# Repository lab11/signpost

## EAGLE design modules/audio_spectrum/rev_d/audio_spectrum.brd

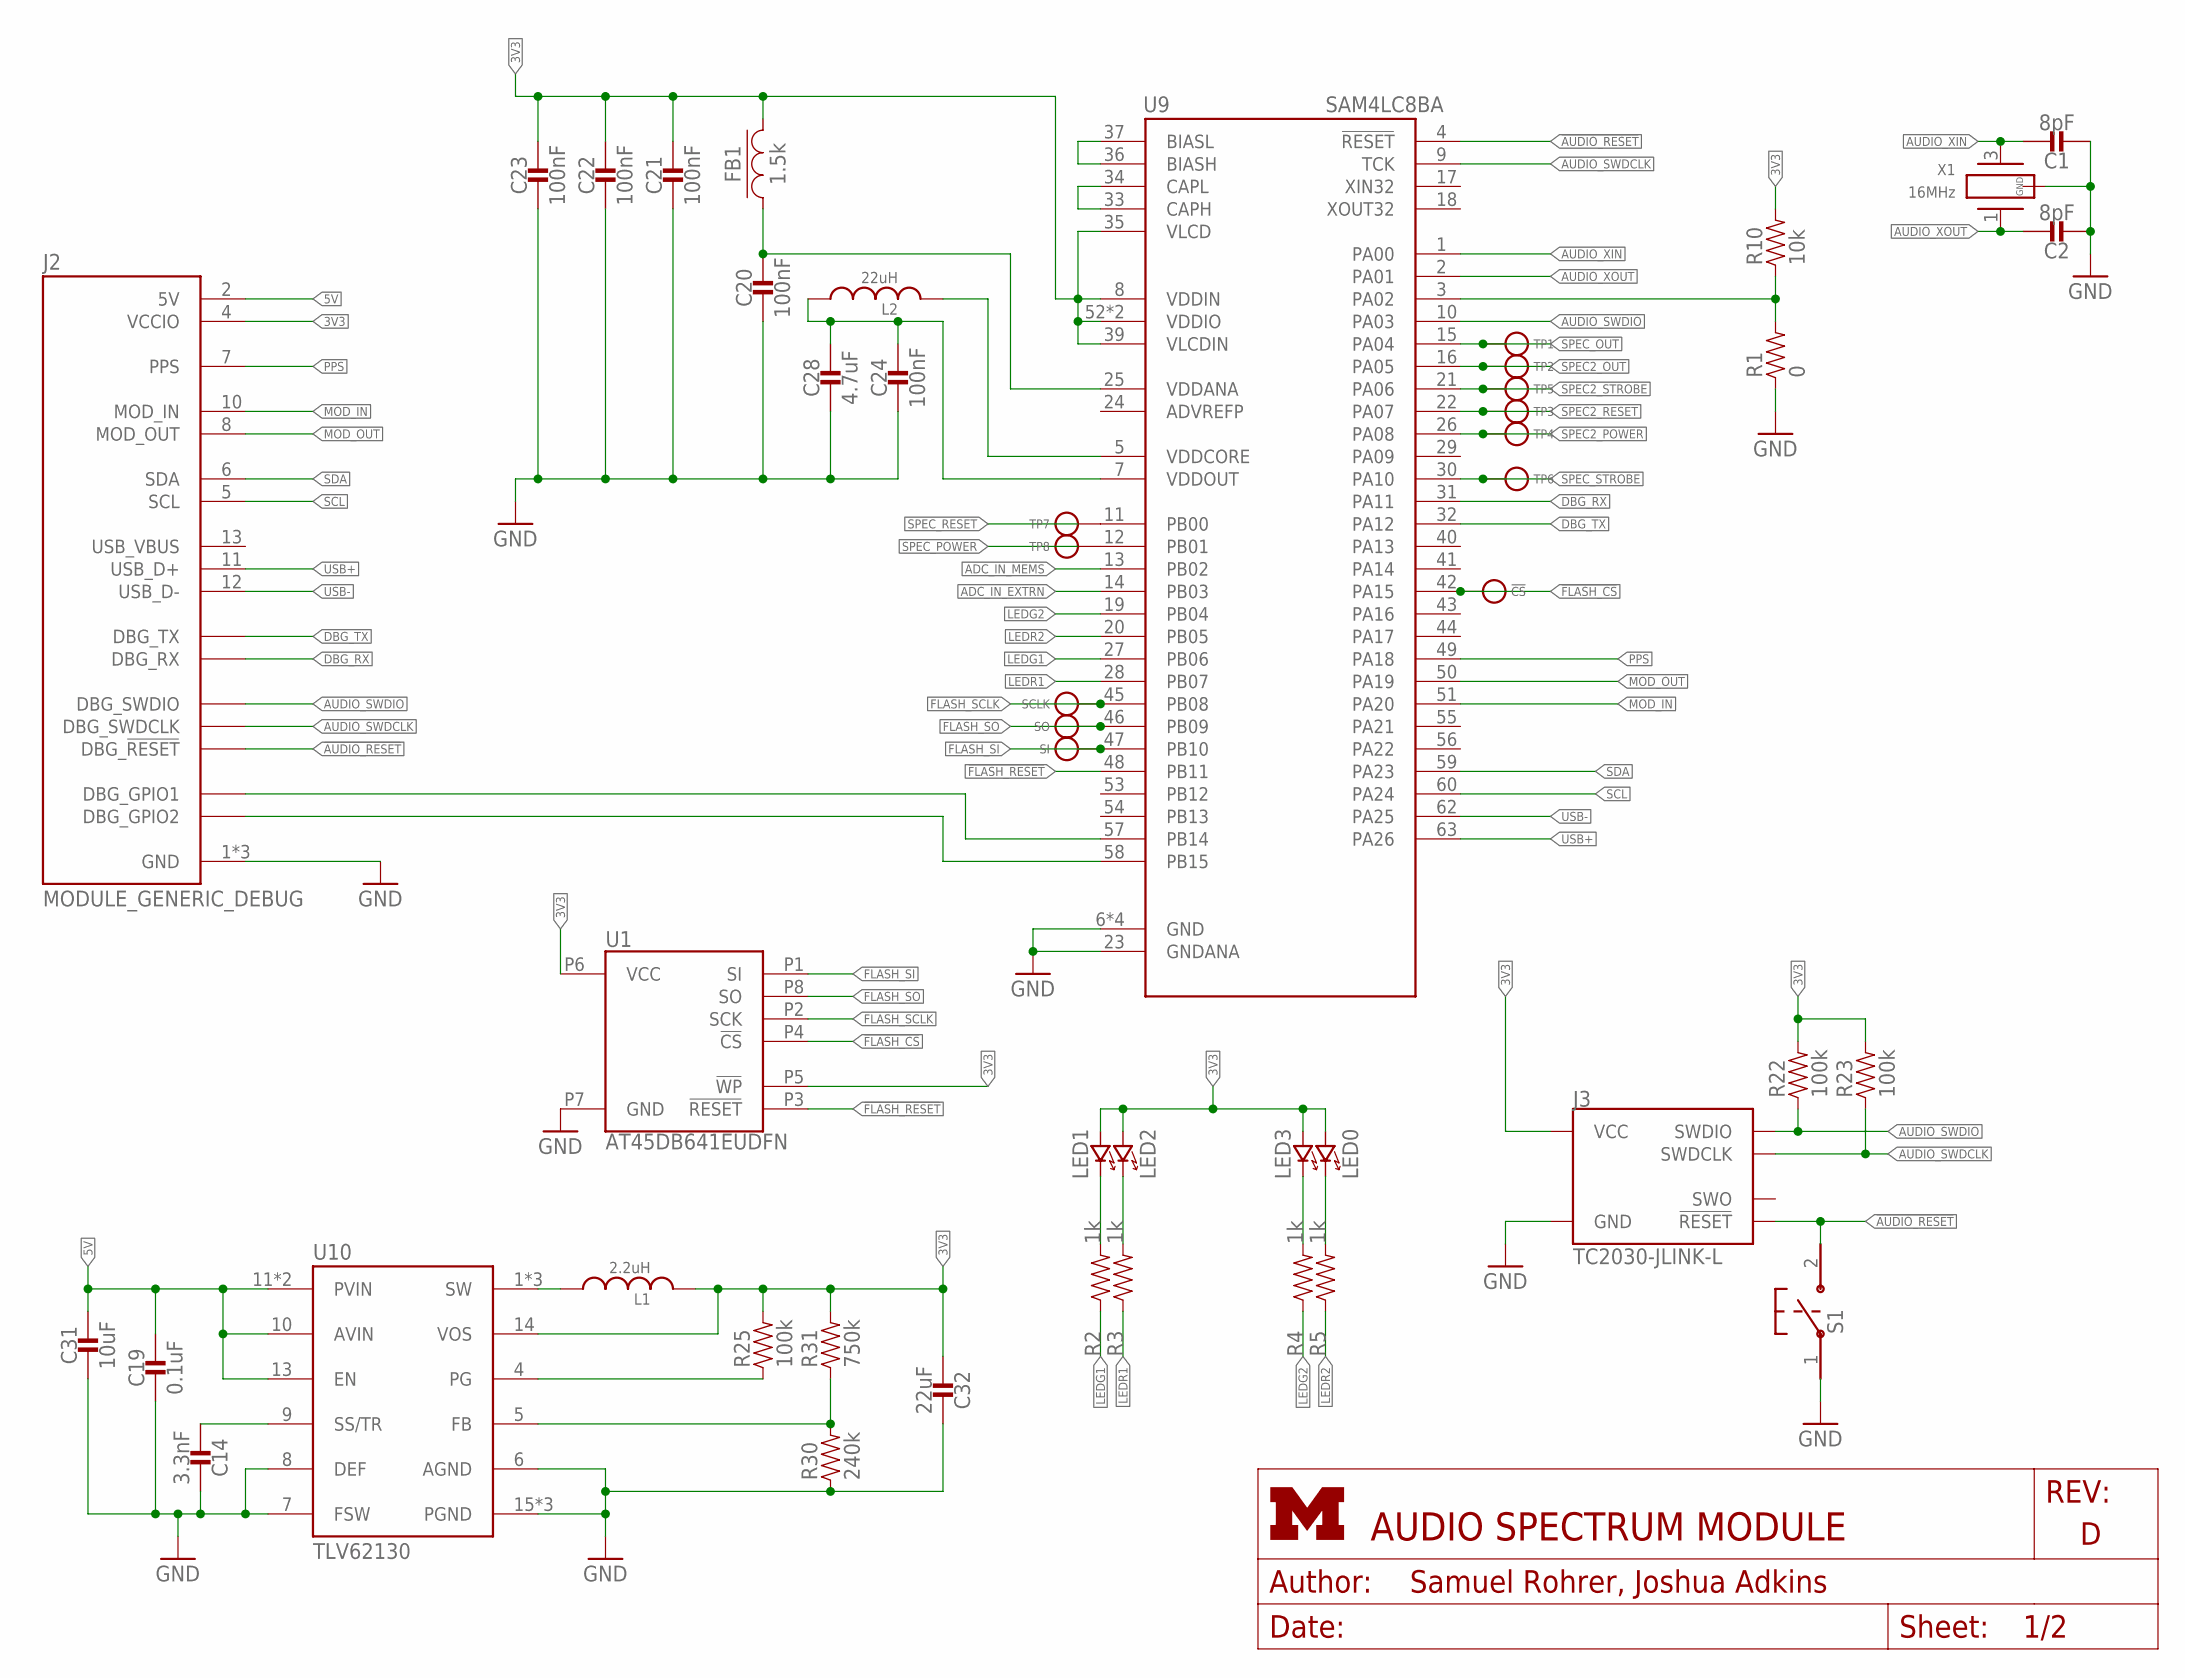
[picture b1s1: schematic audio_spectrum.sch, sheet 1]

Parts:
!CS: TEST_POINT_0.040IN; TESTPOINT_0.040IN
C1, C2: 8pF; 0402_CAP; DIGIKEY 490-8230-1-ND
C14: 3.3nF; 0603_CAP; DIGIKEY 490-1503-1-ND
C19: 0.1uF; 0603_CAP; DIGIKEY 490-1532-1-ND
C20, C21, C22, C23: 100nF; 0603_CAP; DIGIKEY 490-1532-1-ND
C24: 100nF; 0402_CAP; DIGIKEY 490-10777-1-ND
C28: 4.7uF; 0402_CAP; DIGIKEY 490-13252-1-ND
C31: 10uF; 0603_CAP; DIGIKEY 490-6405-1-ND
C32: 22uF; 0603_CAP; DIGIKEY 490-13241-1-ND
FB1: 1.5k; 0402_CAP; DIGIKEY 490-5216-1-ND
J2: MODULE_GENERIC_DEBUG
J3: TC2030-JLINK-L; TC2030-IDC
L1: 2.2uH; IHL-1212BZ-11
L2: 22uH; 1212
LED0, LED2: LED0603; LED-0603; DIGIKEY 160-1447-1-ND
LED1, LED3: LED0603; LED-0603; DIGIKEY 160-1446-1-ND
R1: 0; 0603-RES; DIGIKEY 1276-3431-1-ND
R2: 1k; 0603-RES; DIGIKEY RHM1.0KDCT-N
R3, R4, R5: 1k; 0603-RES; DIGIKEY RHM1.0KDCT-ND
R10: 10k; 0603-RES; DIGIKEY RHM10.0KHCT-ND
R22, R23, R25: 100k; 0603-RES; DIGIKEY RHM100KCGCT-ND
R30: 240k; 0603-RES; DIGIKEY RHM240KCFCT-ND
R31: 750k; 0603-RES; DIGIKEY RHM750KCFCT-ND
S1: B3U-1000P
SCLK: TEST_POINT_0.040IN; TESTPOINT_0.040IN
SI: TEST_POINT_0.040IN; TESTPOINT_0.040IN
SO: TEST_POINT_0.040IN; TESTPOINT_0.040IN
TP1, TP2, TP3, TP4, TP5, TP6, TP7, TP8: TEST_POINT_0.040IN; TESTPOINT_0.040IN
U1: AT45DB641EUDFN; UDFN-8-5MMX6MM
U9: SAM4LC8BA; QFN-64-9MM
U10: TLV62130; TQFN-16/3MM
X1: 16MHz; FHXXX

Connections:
3V3: C21.1, C22.1, C23.1, C32.2, FB1.2, J2.4 (VCCIO), J3.1 (VCC), L1.P$2 (2), LED0.A (ANODE), LED1.A (ANODE), LED2.A (ANODE), LED3.A (ANODE), R10.2, R22.2, R23.2, R25.2, R31.2, U1.P5 (!WP), U1.P6 (VCC), U9.8 (VDDIN), U9.35 (VLCD), U9.39 (VLCDIN), U9.52 (VDDIO), U9.61 (VDDIO), U10.14 (VOS); also elsewhere on the board
3VSWOUT: L1.P$1 (1), U10.1 (SW), U10.2 (SW), U10.3 (SW)
5V: C19.1, C31.1, J2.2 (5V), U10.10 (AVIN), U10.11 (PVIN), U10.12 (PVIN), U10.13 (EN)
!AUDIO_RESET: J2.20 (DBG_!RESET), J3.3 (!RESET), S1.2, U9.4 (!RESET)
!FLASH_CS: !CS.TESTPOINT, U1.P4 (!CS), U9.42 (PA15)
!FLASH_RESET: U1.P3 (!RESET), U9.48 (PB11)
ADC_IN_EXTRN: U9.14 (PB03); also elsewhere on the board
ADC_IN_MEMS: U9.13 (PB02); also elsewhere on the board
AUDIO_SWDCLK: J2.21 (DBG_SWDCLK), J3.4 (SWDCLK), R23.1, U9.9 (TCK)
AUDIO_SWDIO: J2.22 (DBG_SWDIO), J3.2 (SWDIO), R22.1, U9.10 (PA03)
AUDIO_XIN: C1.1, U9.1 (PA00), X1.3 (2)
AUDIO_XOUT: C2.1, U9.2 (PA01), X1.1
CONTROLLER_BUCK/LDO_N: R1.2, R10.1, U9.3 (PA02)
DBG_GPIO1: J2.16 (DBG_GPIO1), U9.57 (PB14)
DBG_GPIO2: J2.19 (DBG_GPIO2), U9.58 (PB15)
DBG_RX: J2.18 (DBG_RX), U9.31 (PA11)
DBG_TX: J2.17 (DBG_TX), U9.32 (PA12)
FLASH_SCLK: SCLK.TESTPOINT, U1.P2 (SCK), U9.45 (PB08)
FLASH_SI: SI.TESTPOINT, U1.P1 (SI), U9.47 (PB10)
FLASH_SO: SO.TESTPOINT, U1.P8 (SO), U9.46 (PB09)
GND: C1.2, C2.2, C14.1, C19.2, C20.2, C21.2, C22.2, C23.2, C24.2, C28.2, C31.2, C32.1, J2.1 (GND), J2.14 (GND), J2.15 (GND), J3.5 (GND), R1.1, R30.1, S1.1, U1.P7 (GND), U9.6 (GND), U9.23 (GNDANA), U9.38 (GND), U9.64 (GND), U9.GND, U10.6 (AGND), U10.7 (FSW), U10.8 (DEF), U10.15 (PGND), U10.16 (PGND), U10.GND, X1.2 (GND), X1.4 (GND); also elsewhere on the board
LEDG1: R2.1, U9.27 (PB06)
LEDG2: R4.1, U9.19 (PB04)
LEDR1: R3.1, U9.28 (PB07)
LEDR2: R5.1, U9.20 (PB05)
MOD_IN: J2.10 (MOD_IN), U9.51 (PA20)
MOD_OUT: J2.8 (MOD_OUT), U9.50 (PA19)
unnamed: L2.P$2 (2), U9.5 (VDDCORE)
unnamed: LED1.C (CATHODE), R2.2
unnamed: TP7.TESTPOINT, U9.11 (PB00)
unnamed: LED2.C (CATHODE), R3.2
unnamed: TP8.TESTPOINT, U9.12 (PB01)
unnamed: LED0.C (CATHODE), R5.2
unnamed: C20.1, FB1.1, U9.25 (VDDANA)
unnamed: LED3.C (CATHODE), R4.2
unnamed: C14.2, U10.9 (SS/TR)
unnamed: R25.1, U10.4 (PG)
unnamed: R30.2, R31.1, U10.5 (FB)
unnamed: C24.1, C28.1, L2.P$1 (1), U9.7 (VDDOUT)
unnamed: U9.36 (BIASH), U9.37 (BIASL)
unnamed: U9.33 (CAPH), U9.34 (CAPL)
PPS: J2.7 (PPS), U9.49 (PA18)
SCL: J2.5 (SCL), U9.60 (PA24)
SDA: J2.6 (SDA), U9.59 (PA23)
SPEC2_OUT: TP2.TESTPOINT, U9.16 (PA05); also elsewhere on the board
SPEC2_POWER: TP4.TESTPOINT, U9.26 (PA08); also elsewhere on the board
SPEC2_RESET: TP3.TESTPOINT, U9.22 (PA07); also elsewhere on the board
SPEC2_STROBE: TP5.TESTPOINT, U9.21 (PA06); also elsewhere on the board
SPEC_OUT: TP1.TESTPOINT, U9.15 (PA04); also elsewhere on the board
SPEC_STROBE: TP6.TESTPOINT, U9.30 (PA10); also elsewhere on the board
USB+: J2.11 (USB_D+), U9.63 (PA26)
USB-: J2.12 (USB_D-), U9.62 (PA25)

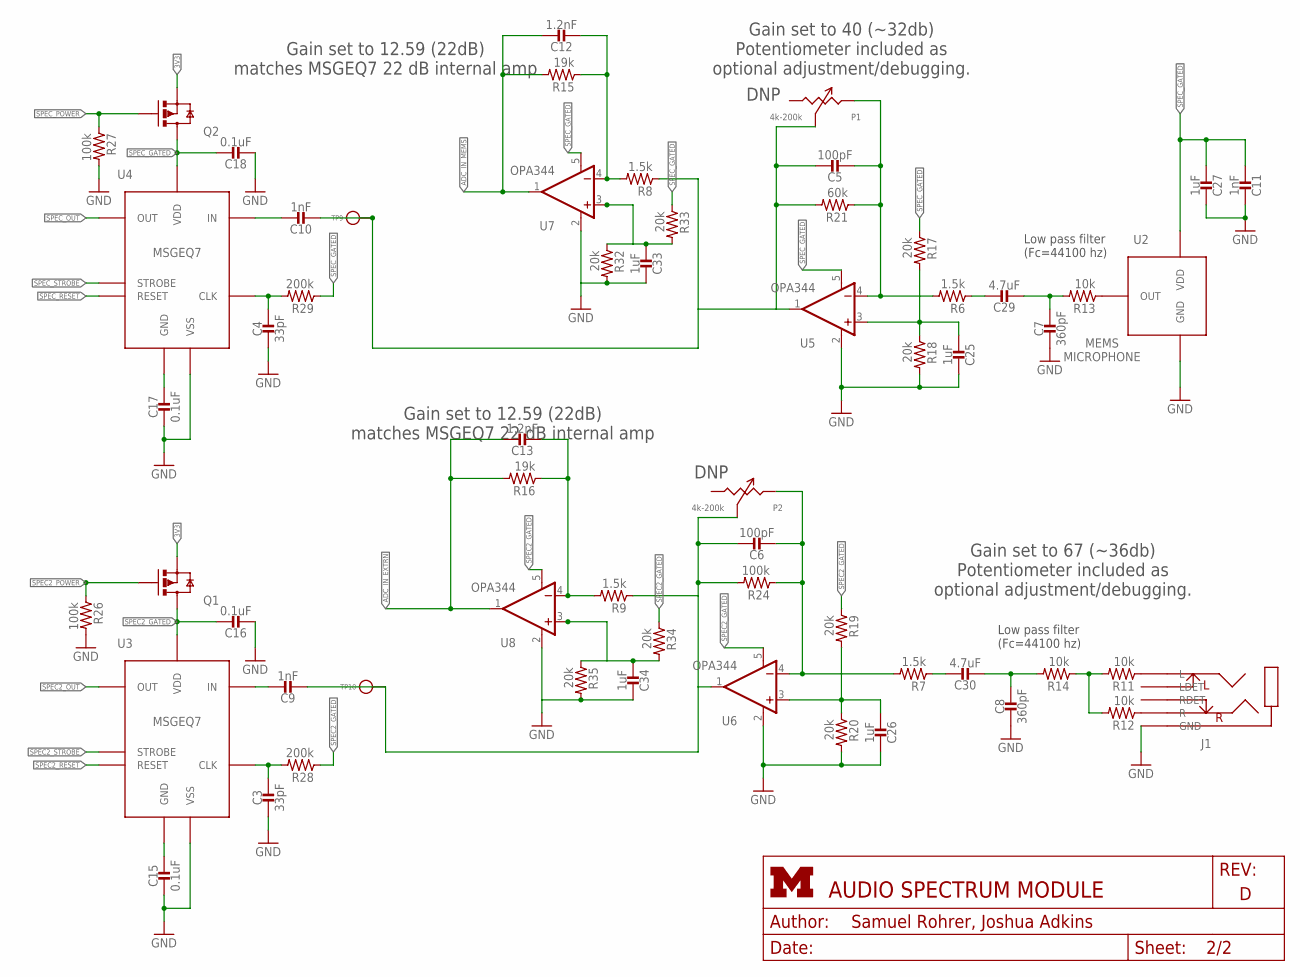
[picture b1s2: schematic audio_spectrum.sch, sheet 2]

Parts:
C3, C4: 33pF; 0603_CAP; DIGIKEY 490-1415-1-ND
C5, C6: 100pF; 0603_CAP; DIGIKEY 490-1427-1-ND
C7, C8: 360pF; 0603_CAP; DIGIKEY 490-1440-1-ND
C9, C10, C11: 1nF; 0603_CAP; DIGIKEY 490-1494-1-ND
C12, C13: 1.2nF; 0603_CAP; DIGIKEY 490-13298-1-ND
C15, C16, C17, C18: 0.1uF; 0603_CAP; DIGIKEY 490-1532-1-ND
C25, C26, C27, C33, C34: 1uF; 0603_CAP; DIGIKEY 490-1536-1-ND
C29, C30: 4.7uF; 0603_CAP; DIGIKEY 490-3297-1-ND
J1: AUDIO-JACK-VERTICAL
P1, P2: 4k-200k; TC33X-2
Q1, Q2: NX3008PBK; SOT23-3
R6, R7, R8, R9: 1.5k; 0603-RES; DIGIKEY RHM1.5KCGCT-ND
R11, R12, R13, R14: 10k; 0603-RES; DIGIKEY RHM10.0KHCT-ND
R15, R16: 19k; 0603-RES; DIGIKEY RHM19.1KCFCT-ND
R17, R18, R19, R20, R32, R33, R34, R35: 20k; 0603-RES; DIGIKEY RHM20KCGCT-ND
R21: 60k; 0603-RES; DIGIKEY RHM60.4KCLCT-ND
R24, R26, R27: 100k; 0603-RES; DIGIKEY RHM100KCGCT-ND
R28, R29: 200k; 0603-RES; DIGIKEY RHM200KCFCT-ND
TP9, TP10: TEST_POINT_0.040IN; TESTPOINT_0.040IN
U2: MP23AB02B
U3, U4: MSGEQ7; DIP-8
U5, U6, U7, U8: OPA344; SOT23-5; DIGIKEY OPA344NACT-ND

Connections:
3V3: Q1.2 (S), Q2.2 (S); also elsewhere on the board
ADC_IN_EXTRN: C13.1, R16.2, U8.1 (OUT); also elsewhere on the board
ADC_IN_MEMS: C12.1, R15.2, U7.1 (OUT); also elsewhere on the board
GND: C3.2, C4.2, C7.2, C8.2, C11.1, C15.2, C16.2, C17.2, C18.2, C25.1, C26.1, C27.1, C33.1, C34.1, J1.5 (GND), R18.2, R20.2, R26.2, R27.2, R32.2, R35.2, U2.3 (GND), U3.2 (VSS), U4.2 (VSS), U5.2 (V-), U6.2 (V-), U7.2 (V-), U8.2 (V-); also elsewhere on the board
N87: C6.1, C9.2, P2.3 (W), R9.1, R24.2, TP10.TESTPOINT, U6.1 (OUT)
N90: C5.1, C10.2, P1.3 (W), R8.1, R21.2, TP9.TESTPOINT, U5.1 (OUT)
unnamed: C15.1, U3.6 (GND)
unnamed: C3.1, R28.2, U3.8 (CLK)
unnamed: C9.1, U3.5 (IN)
unnamed: C7.1, C29.2, R13.2
unnamed: C4.1, R29.2, U4.8 (CLK)
unnamed: C10.1, U4.5 (IN)
unnamed: C13.2, R9.2, R16.1, U8.4 (-IN)
unnamed: C25.2, R17.2, R18.1, U5.3 (+IN)
unnamed: R11.2, R12.2, R14.1
unnamed: C26.2, R19.2, R20.1, U6.3 (+IN)
unnamed: C5.2, P1.2 (CW), R6.2, R21.1, U5.4 (-IN)
unnamed: C29.1, R6.1
unnamed: C6.2, P2.2 (CW), R7.2, R24.1, U6.4 (-IN)
unnamed: C30.1, R7.1
unnamed: J1.1 (R), R12.1
unnamed: J1.4 (L), R11.1
unnamed: R13.1, U2.1 (OUT)
unnamed: C17.1, U4.6 (GND)
unnamed: C8.1, C30.2, R14.2
unnamed: C12.2, R8.2, R15.1, U7.4 (-IN)
unnamed: C33.2, R32.1, R33.2, U7.3 (+IN)
unnamed: C34.2, R34.2, R35.1, U8.3 (+IN)
SPEC2_GATED: C16.1, Q1.3 (D), R19.1, R28.1, R34.1, U3.1 (VDD), U6.5 (V+), U8.5 (V+)
SPEC2_OUT: U3.3 (OUT); also elsewhere on the board
SPEC2_POWER: Q1.1 (G), R26.1; also elsewhere on the board
SPEC2_RESET: U3.7 (RESET); also elsewhere on the board
SPEC2_STROBE: U3.4 (STROBE); also elsewhere on the board
SPEC_GATED: C11.2, C18.1, C27.2, Q2.3 (D), R17.1, R29.1, R33.1, U2.2 (VDD), U4.1 (VDD), U5.5 (V+), U7.5 (V+)
SPEC_OUT: U4.3 (OUT); also elsewhere on the board
SPEC_POWER: Q2.1 (G), R27.1
SPEC_RESET: U4.7 (RESET)
SPEC_STROBE: U4.4 (STROBE); also elsewhere on the board

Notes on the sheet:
DNP
Gain set to 40 (~32db) Potentiometer included as optional adjustment/debugging.
Gain set to 67 (~36db) Potentiometer included as optional adjustment/debugging.
Low pass filter (Fc=44100 hz)
Gain set to 12.59 (22dB) matches MSGEQ7 22 dB internal amp

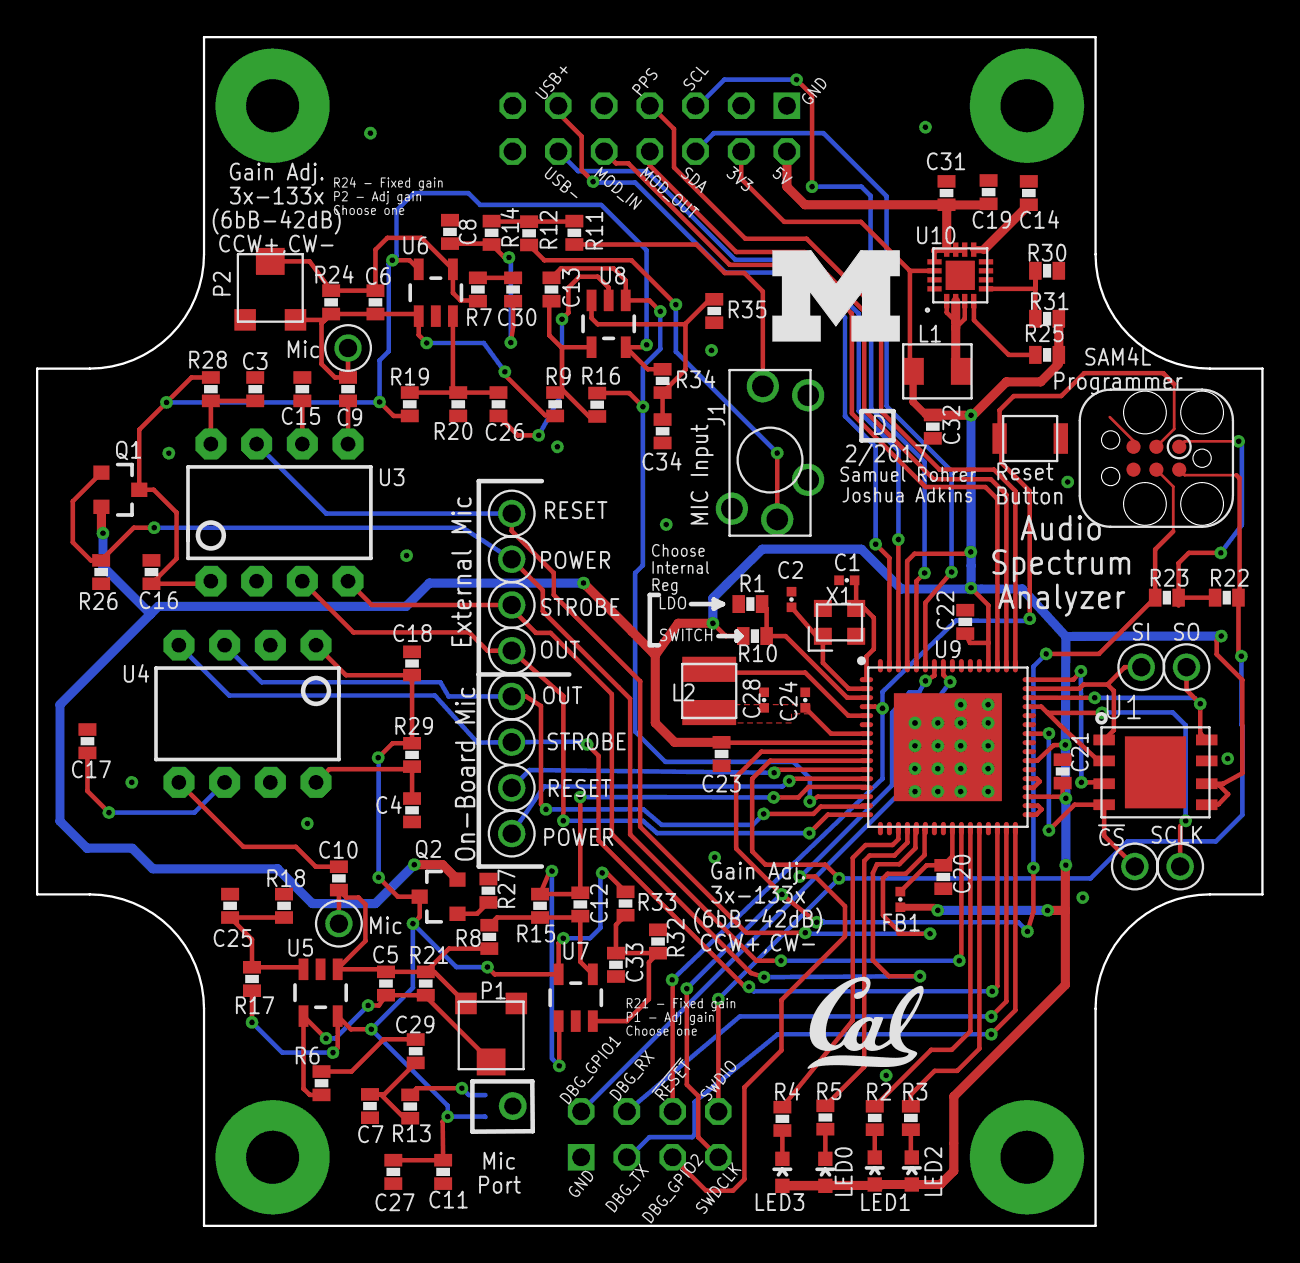
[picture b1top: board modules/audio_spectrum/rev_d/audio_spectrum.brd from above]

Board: 4 copper layers, 68.1 x 66.0 mm, 111 parts (1 on the bottom side), 79 nets.

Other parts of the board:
U$1: UMICH_SOLID_200MIL
U$2: UCB_CAL_200MIL

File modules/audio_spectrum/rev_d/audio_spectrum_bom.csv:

"# Bill of Materials",,,,,,,,
"# Converted from audio_spectrum_bom.xlsx",,,,,,,,
"# Generated by bom_to_text.py",,,,,,,,
"#",,,,,,,,
Qty,Value,Device,Package,Parts,Description,DIGIKEY,MOUSER,NEWARK
2,8pF,CAPACITOR0402_CAP,0402_CAP,"C1, C2",0402 Capacitor,490-8230-1-ND,,
2,1.2nF,CAPACITOR0603_CAP,0603_CAP,"C12, C13",0402 Capacitor,490-13298-1-ND,,
1,3.3nF,CAPACITOR0603_CAP,0603_CAP,C14,0402 Capacitor,490-1503-1-ND,,
5,0.1uF,CAPACITOR0603_CAP,0603_CAP,"C15, C16, C17, C18, C19",0402 Capacitor,490-1532-1-ND,,
4,100nF,CAPACITOR0603_CAP,0603_CAP,"C20, C21, C22, C23",0402 Capacitor,490-1532-1-ND,,
1,100nF,CAPACITOR0402_CAP,0402_CAP,C24,0402 Capacitor,490-10777-1-ND,,
5,1uF,CAPACITOR0603_CAP,0603_CAP,"C25, C26, C27, C33, C34",0402 Capacitor,490-1536-1-ND,,
1,4.7uF,CAPACITOR0402_CAP,0402_CAP,C28,0402 Capacitor,490-13252-1-ND,,
2,4.7uF,CAPACITOR0603_CAP,0603_CAP,"C29, C30",0402 Capacitor,490-3297-1-ND,,
2,33pF,CAPACITOR0603_CAP,0603_CAP,"C3, C4",0402 Capacitor,490-1415-1-ND,,
1,10uF,CAPACITOR0603_CAP,0603_CAP,C31,0402 Capacitor,490-6405-1-ND,,
1,22uF,CAPACITOR0603_CAP,0603_CAP,C32,0402 Capacitor,490-13241-1-ND,,
2,100pF,CAPACITOR0603_CAP,0603_CAP,"C5, C6",0402 Capacitor,490-1427-1-ND,,
2,360pF,CAPACITOR0603_CAP,0603_CAP,"C7, C8",0402 Capacitor,490-1440-1-ND,,
3,1nF,CAPACITOR0603_CAP,0603_CAP,"C9, C10, C11",0402 Capacitor,490-1494-1-ND,,
1,1.5k,FERRITE_BEAD0402,0402_CAP,FB1,,490-5216-1-ND,,
1,AUDIO-JACK-VERTICAL,AUDIO-JACK-VERTICAL,AUDIO-JACK-VERTICAL,J1,A vertical audio jack,,806-STX-3790-5N,
1,MODULE_GENERIC_DEBUG,MODULE_GENERIC_DEBUG,MODULE_GENERIC_DEBUG,J2,The debug version of the signpost module header,S9170-ND,,
1,TC2030-JLINK-L,TC2030-JLINK-L,TC2030-IDC,J3,,,,
1,2.2uH,INDUCTORIHL,IHL-1212BZ-11,L1,A very specific inductor,541-1322-1-ND,,
1,22uH,LHQ3NP,1212,L2,LHQ3NP Inductor,490-5350-1-ND,,
2,LED0603,LED0603,LED-0603,"LED0, LED2",LED,160-1447-1-ND,,
2,LED0603,LED0603,LED-0603,"LED1, LED3",LED,160-1446-1-ND,,
2,4k-200k,POTTC33X,TC33X-2,"P1, P2",Potentiometer,TC33X-2-204ECT-ND,,
2,NX3008PBK,NX3008PBK,SOT23-3,"Q1, Q2",MOSFET - P Channel,568-10499-1-ND,"771-NX3008PBK,215",74T4665
1,0,RESISTOR0603_RES,0603-RES,R1,Resistor,1276-3431-1-ND,,
4,10k,RESISTOR0603_RES,0603-RES,"R10, R11, R13, R14",Resistor,RHM10.0KHCT-ND,,
1,10k,RESISTOR0603_RES,0603-RES,R12,Resistor,RHM10.0KHCT-ND ,,
2,19k,RESISTOR0603_RES,0603-RES,"R15, R16",Resistor,RHM19.1KCFCT-ND,,
8,20k,RESISTOR0603_RES,0603-RES,"R17, R18, R19, R20, R32, R33, R34, R35",Resistor,RHM20KCGCT-ND,,
1,1k,RESISTOR0603_RES,0603-RES,R2,Resistor,RHM1.0KDCT-N,,
1,60k,RESISTOR0603_RES,0603-RES,R21,Resistor,RHM60.4KCLCT-ND,,
6,100k,RESISTOR0603_RES,0603-RES,"R22, R23, R24, R25, R26, R27",Resistor,RHM100KCGCT-ND,,
2,200k,RESISTOR0603_RES,0603-RES,"R28, R29",Resistor,RHM200KCFCT-ND,,
3,1k,RESISTOR0603_RES,0603-RES,"R3, R4, R5",Resistor,RHM1.0KDCT-ND,,
1,240k,RESISTOR0603_RES,0603-RES,R30,Resistor,RHM240KCFCT-ND,,
1,750k,RESISTOR0603_RES,0603-RES,R31,Resistor,RHM750KCFCT-ND,,
4,1.5k,RESISTOR0603_RES,0603-RES,"R6, R7, R8, R9",Resistor,RHM1.5KCGCT-ND,,
1,B3U-1000P,B3U-1000P,B3U-1000P,S1,Switch,SW1020CT-ND,,
1,AT45DB641EUDFN,AT45DB641EUDFN,UDFN-8-5MMX6MM,U1,64 Mbit flash memory,AT45DB641E-MHN-TCT-ND,,
1,TLV62130,TLV62130,TQFN-16/3MM,U10,"High Efficient 3A switching step-down regulator. 1V-5V out, 4V-17V in.",296-35978-1-ND,,
1,MP23AB02B,MP23AB02B,MP23AB02B,U2,A pretty normal mems microphone,497-14947-1-ND,,
2,MSGEQ7,MSGEQ7,DIP-8,"U3, U4",A CMOS spectrum analyzer,1568-1335-ND,,
4,OPA344,OPA344,SOT23-5,"U5, U6, U7, U8",Single gate rail-to-rail output op-amp. Inputs extend 300mV past rails.,OPA344NACT-ND,,
1,SAM4LC8BA,SAM4LC8BA,QFN-64-9MM,U9,SAM4L Microcontroller. 64QFN Package. 512 Flash.,ATSAM4LC8BA-MURCT-ND,,
1,16MHz,FH1600015,FHXXX,X1,Pericom Type FH 16 MHz 2.5 x 2.0 mm,FH1600015CT-ND,,

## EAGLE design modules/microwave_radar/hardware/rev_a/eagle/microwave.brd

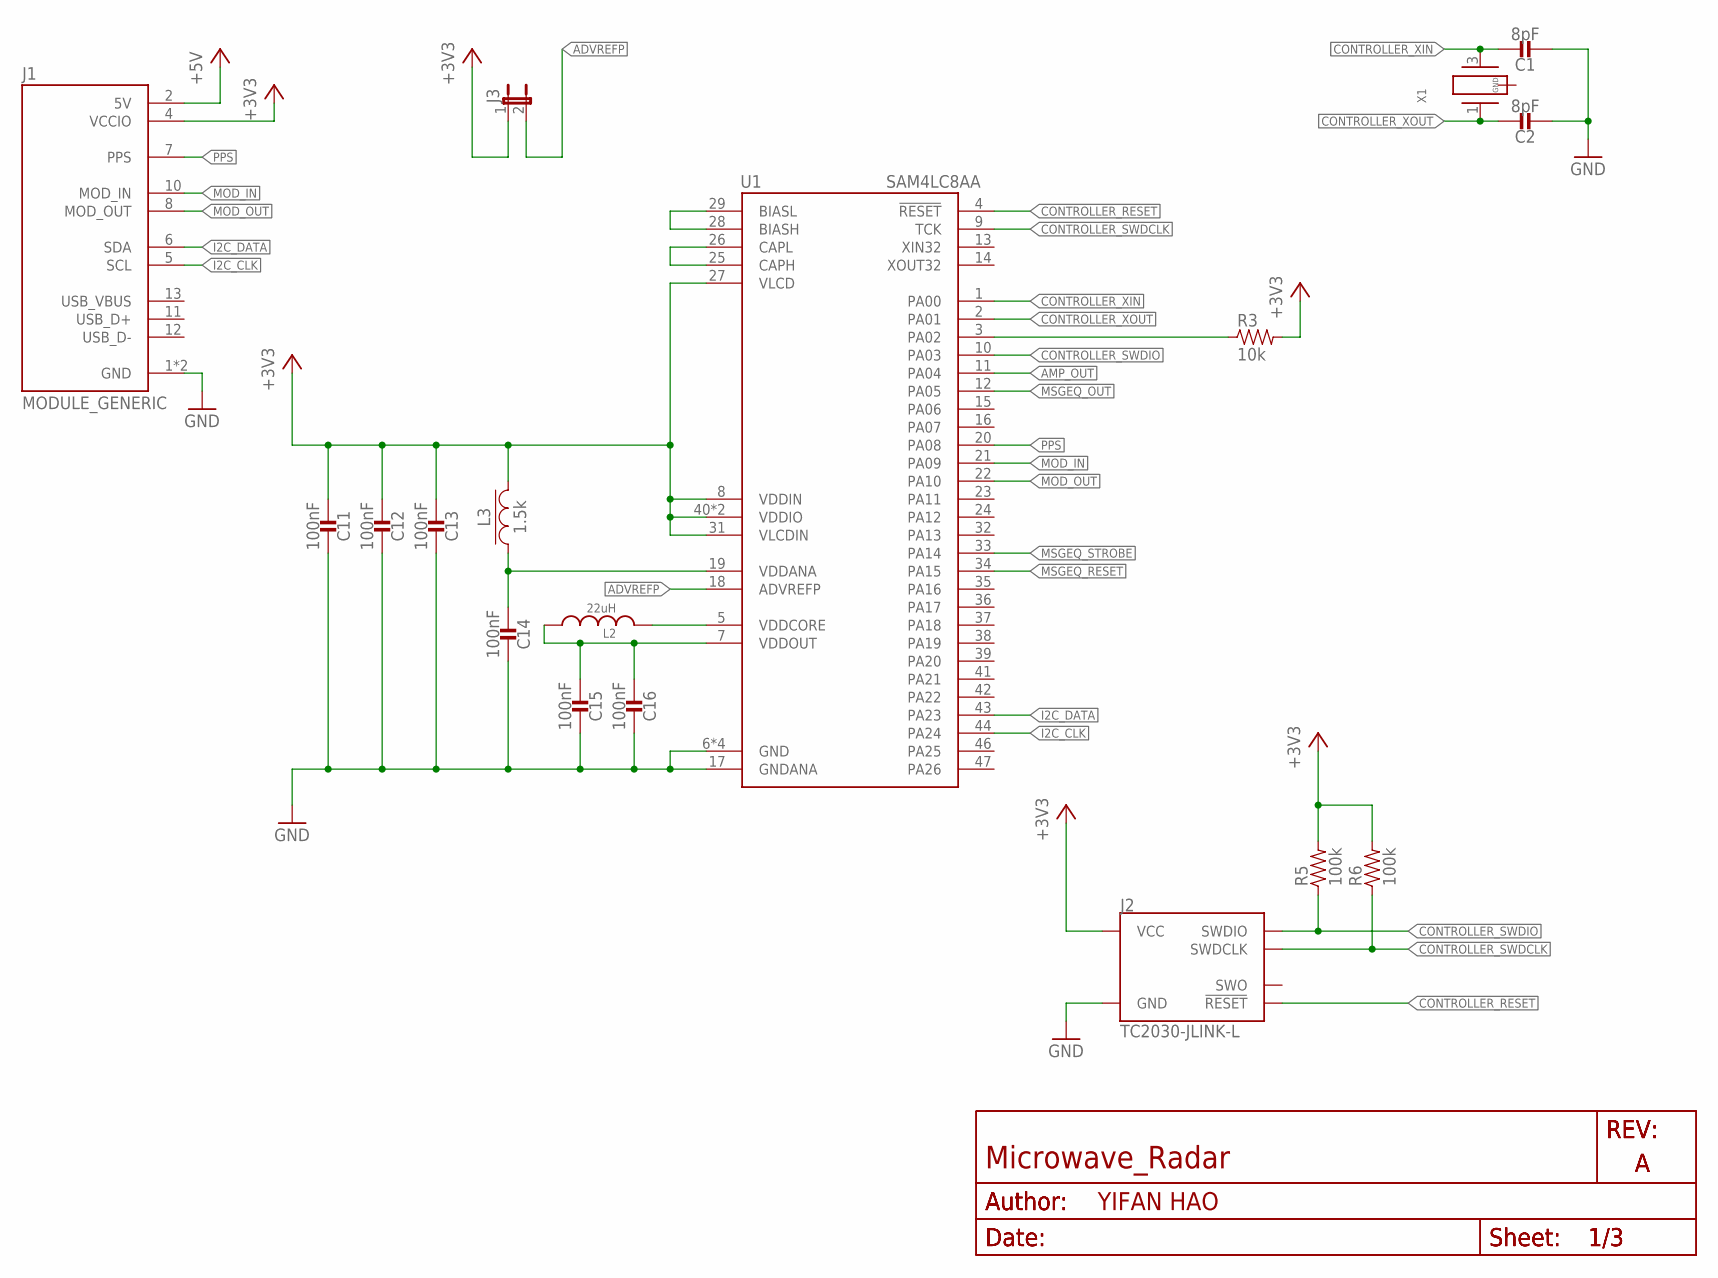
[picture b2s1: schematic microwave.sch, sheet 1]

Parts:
C1, C2: 8pF; 0402_CAP; DIGIKEY 490-8230-1-ND
C11, C12, C13, C14, C16: 100nF; 0402_CAP; DIGIKEY 490-10777-1-ND
C15: 100nF; 0402_CAP; DIGIKEY 490-13252-1-ND
J1: MODULE_GENERIC
J2: TC2030-JLINK-L; TC2030-IDC
J3: JUMPER-2PTH; 1X02
L2: 22uH; 1212
L3: 1.5k; 0402_CAP; DIGIKEY 490-5216-1-ND
R3: 10k; 0402_RES; DIGIKEY 1276-3431-1-ND
R5, R6: 100k; 0402_RES; DIGIKEY 1276-3432-1-ND
U1: SAM4LC8AA; QFN-48-7MM
X1: FH1600015; FHXXX

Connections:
+3V3: C11.2, C12.2, C13.2, J1.4 (VCCIO), J2.1 (VCC), J3.1, L3.2, R3.2, R5.2, R6.2, U1.8 (VDDIN), U1.27 (VLCD), U1.31 (VLCDIN), U1.40 (VDDIO), U1.45 (VDDIO); also elsewhere on the board
+5V: J1.2 (5V); also elsewhere on the board
ADVREFP: J3.2, U1.18 (ADVREFP)
AMP_OUT: U1.11 (PA04); also elsewhere on the board
CONTROLLER_RESET: J2.3 (!RESET), U1.4 (!RESET)
CONTROLLER_SWDCLK: J2.4 (SWDCLK), R6.1, U1.9 (TCK)
CONTROLLER_SWDIO: J2.2 (SWDIO), R5.1, U1.10 (PA03)
CONTROLLER_XIN: C1.1, U1.1 (PA00), X1.3 (2)
CONTROLLER_XOUT: C2.1, U1.2 (PA01), X1.1
GND: C1.2, C2.2, C11.1, C12.1, C13.1, C14.1, C15.1, C16.1, J1.1 (GND), J1.14 (GND), J2.5 (GND), U1.6 (GND), U1.17 (GNDANA), U1.30 (GND), U1.48 (GND), U1.THERMAL (GND); also elsewhere on the board
I2C_CLK: J1.5 (SCL), U1.44 (PA24)
I2C_DATA: J1.6 (SDA), U1.43 (PA23)
MOD_IN: J1.10 (MOD_IN), U1.21 (PA09)
MOD_OUT: J1.8 (MOD_OUT), U1.22 (PA10)
MSGEQ_OUT: U1.12 (PA05); also elsewhere on the board
MSGEQ_RESET: U1.34 (PA15); also elsewhere on the board
MSGEQ_STROBE: U1.33 (PA14); also elsewhere on the board
unnamed: L2.P$2 (2), U1.5 (VDDCORE)
unnamed: C15.2, C16.2, L2.P$1 (1), U1.7 (VDDOUT)
unnamed: U1.28 (BIASH), U1.29 (BIASL)
unnamed: U1.25 (CAPH), U1.26 (CAPL)
unnamed: C14.2, L3.1, U1.19 (VDDANA)
unnamed: R3.1, U1.3 (PA02)
PPS: J1.7 (PPS), U1.20 (PA08)

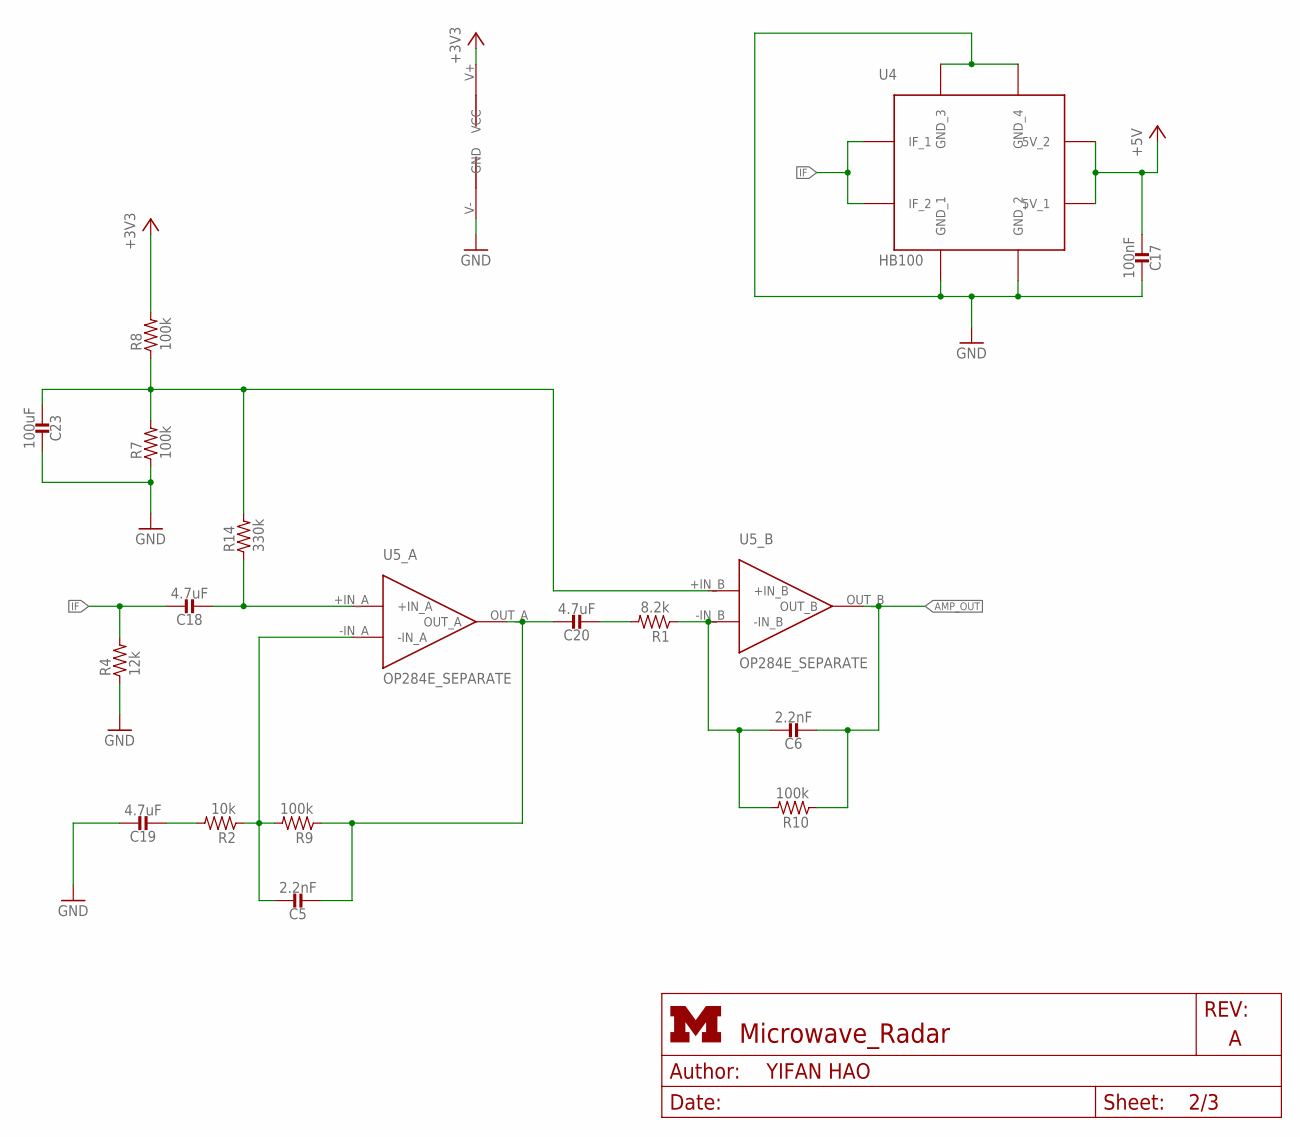
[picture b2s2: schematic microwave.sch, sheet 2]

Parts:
C5, C6: 2.2nF; 0402_CAP; DIGIKEY 490-11418-1-ND
C17: 100nF; 0402_CAP; DIGIKEY 490-10777-1-ND
C18, C19, C20: 4.7uF; 0402_CAP; DIGIKEY 1276-1481-1-ND
C23: 100uF; 1210_CAP; DIGIKEY 490-3390-1-ND
R1: 8.2k; 0402_RES; DIGIKEY 311-8.20KLRCT-ND
R2: 10k; 0402_RES; DIGIKEY 1276-3431-1-ND
R4: 12k; 0402_RES; DIGIKEY 1276-4122-1-ND
R7, R8, R9, R10: 100k; 0402_RES; DIGIKEY 1276-3432-1-ND
R14: 330k; 0402_RES; DIGIKEY 1276-4244-1-ND
U4: HB100; DIGIKEY SAM1067-02-ND
U5: OP284E_SEPARATE; DIGIKEY OP284ESZ-ND

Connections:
+3V3: R8.2, U5.V+ (VCC); also elsewhere on the board
+5V: C17.2, U4.5V_1, U4.5V_2; also elsewhere on the board
AMP_OUT: C6.2, R10.1, U5.OUT_B; also elsewhere on the board
GND: C17.1, C19.1, C23.1, R4.1, R7.1, U4.GND_1, U4.GND_2, U4.GND_3, U4.GND_4, U5.V- (GND); also elsewhere on the board
IF: C18.1, R4.2, U4.IF_1, U4.IF_2; also elsewhere on the board
unnamed: C23.2, R7.2, R8.1, R14.2, U5.+IN_B
unnamed: C18.2, R14.1, U5.+IN_A
unnamed: C5.1, R2.1, R9.2, U5.-IN_A
unnamed: C19.2, R2.2
unnamed: C5.2, C20.1, R9.1, U5.OUT_A
unnamed: C20.2, R1.2
unnamed: C6.1, R1.1, R10.2, U5.-IN_B

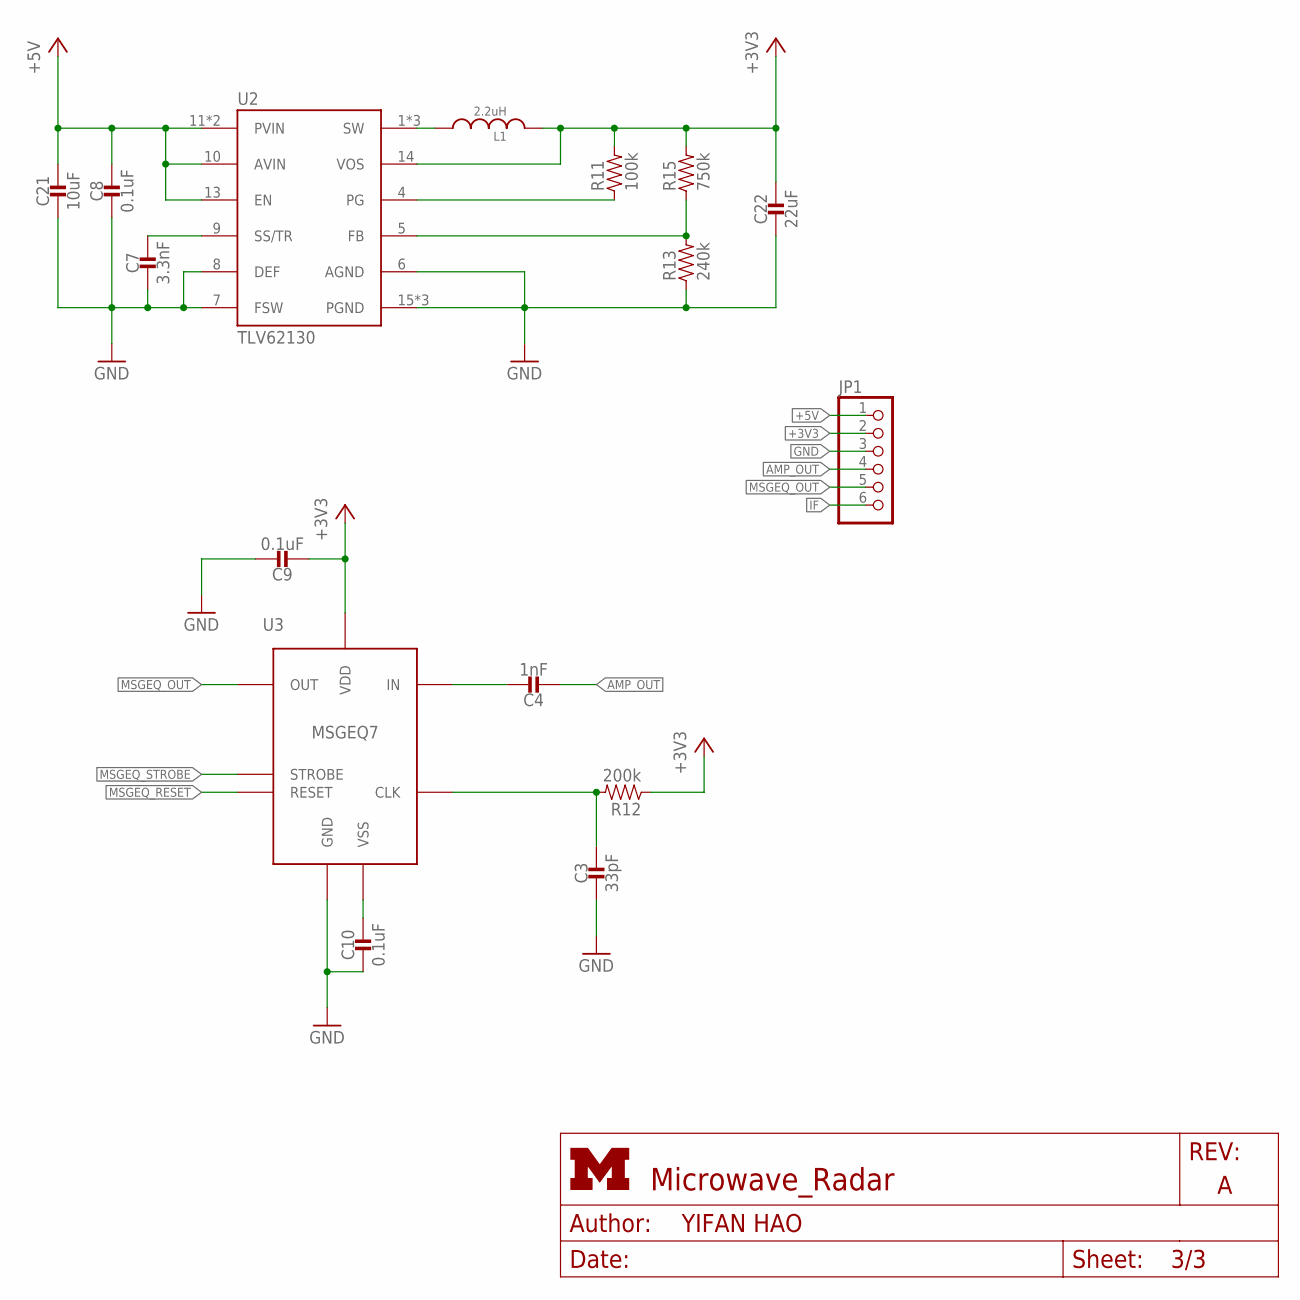
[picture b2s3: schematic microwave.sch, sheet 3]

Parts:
C3: 33pF; 0603_CAP; DIGIKEY 490-1415-1-ND
C4: 1nF; 0603_CAP; DIGIKEY 490-1494-1-ND
C7: 3.3nF; 0402_CAP; DIGIKEY 490-3248-1-ND
C8: 0.1uF; 0402_CAP; DIGIKEY 490-5920-1-ND
C9, C10: 0.1uF; 0603_CAP; DIGIKEY 490-1532-1-ND
C21: 10uF; 0805_CAP; DIGIKEY 490-5523-1-ND
C22: 22uF; 0603_CAP; DIGIKEY 1276-1193-1-ND
JP1: PINHD-1X6; 1X06
L1: 2.2uH; IHL-1212BZ-11
R11: 100k; 0402_RES; DIGIKEY P100KJCT-ND
R12: 200k; 0603-RES; DIGIKEY RHM200KCFCT-ND
R13: 240k; 0402_RES; DIGIKEY P240KLCT-ND
R15: 750k; 0402_RES; DIGIKEY P750KLCT-ND
U2: TLV62130; TQFN-16/3MM
U3: MSGEQ7; DIP-8

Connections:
+3V3: C9.2, C22.1, JP1.2, L1.P$2 (2), R11.2, R12.1, R15.2, U2.14 (VOS), U3.1 (VDD); also elsewhere on the board
+5V: C8.1, C21.P$1 (1), JP1.1, U2.10 (AVIN), U2.11 (PVIN), U2.12 (PVIN), U2.13 (EN); also elsewhere on the board
AMP_OUT: C4.2, JP1.4; also elsewhere on the board
GND: C3.2, C7.2, C8.2, C9.1, C10.2, C21.P$2 (2), C22.2, JP1.3, R13.1, U2.6 (AGND), U2.7 (FSW), U2.8 (DEF), U2.15 (PGND), U2.16 (PGND), U2.GND, U3.6 (GND); also elsewhere on the board
IF: JP1.6; also elsewhere on the board
MSGEQ_OUT: JP1.5, U3.3 (OUT); also elsewhere on the board
MSGEQ_RESET: U3.7 (RESET); also elsewhere on the board
MSGEQ_STROBE: U3.4 (STROBE); also elsewhere on the board
unnamed: C3.1, R12.2, U3.8 (CLK)
unnamed: C4.1, U3.5 (IN)
unnamed: C10.1, U3.2 (VSS)
unnamed: C7.1, U2.9 (SS/TR)
unnamed: L1.P$1 (1), U2.1 (SW), U2.2 (SW), U2.3 (SW)
unnamed: R11.1, U2.4 (PG)
unnamed: R13.2, R15.1, U2.5 (FB)

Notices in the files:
parts and their libraries:
SparkFun-AnalogIC: Licensing: CC v3.0 Share-Alike You are welcome to use this library for commercial purposes.
